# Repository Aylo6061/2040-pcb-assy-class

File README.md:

# 2040pad

An RP2040 macropad, and the board you build in my hands-on PCB soldering class.

## Features

- RP2040 microcontroller with USB-C
- 12 Choc key switches
- 12 SK6812MINI-E RGB LEDs
- PEC11R rotary encoder with push switch
- 128x32 SSD1306 OLED
- QMK firmware

## What's here

| Path | Contents |
|---|---|
| `2040pad/` | KiCad schematic and board, plus `gerbs.zip` |
| `firmware/qmk/2040pad/` | QMK keyboard definition, with build and flashing steps |
| `2040pad_assembly.html`, `2040pad_assembly.pdf` | Soldering and assembly guide |
| `docs/` | [Class web page](https://aylo6061.github.io/2040-pcb-assy-class/) |

The case design is coming soon.

## Status

The first board was built on 2026-11-05, and everything works.

## Credits and license

Based on the [Adafruit MacroPad RP2040](https://github.com/adafruit/Adafruit-MacroPad-RP2040-PCB),
designed by Limor Fried/Ladyada for Adafruit Industries. This is not an Adafruit
product, and Adafruit doesn't support or endorse it.

The hardware is released under Creative Commons Attribution-ShareAlike 3.0.
See [license.txt](license.txt).

The firmware is released under GPL-2.0-or-later. It is based on QMK's
`keyboards/adafruit/macropad` definition, Copyright 2022 Jose Pablo Ramirez.

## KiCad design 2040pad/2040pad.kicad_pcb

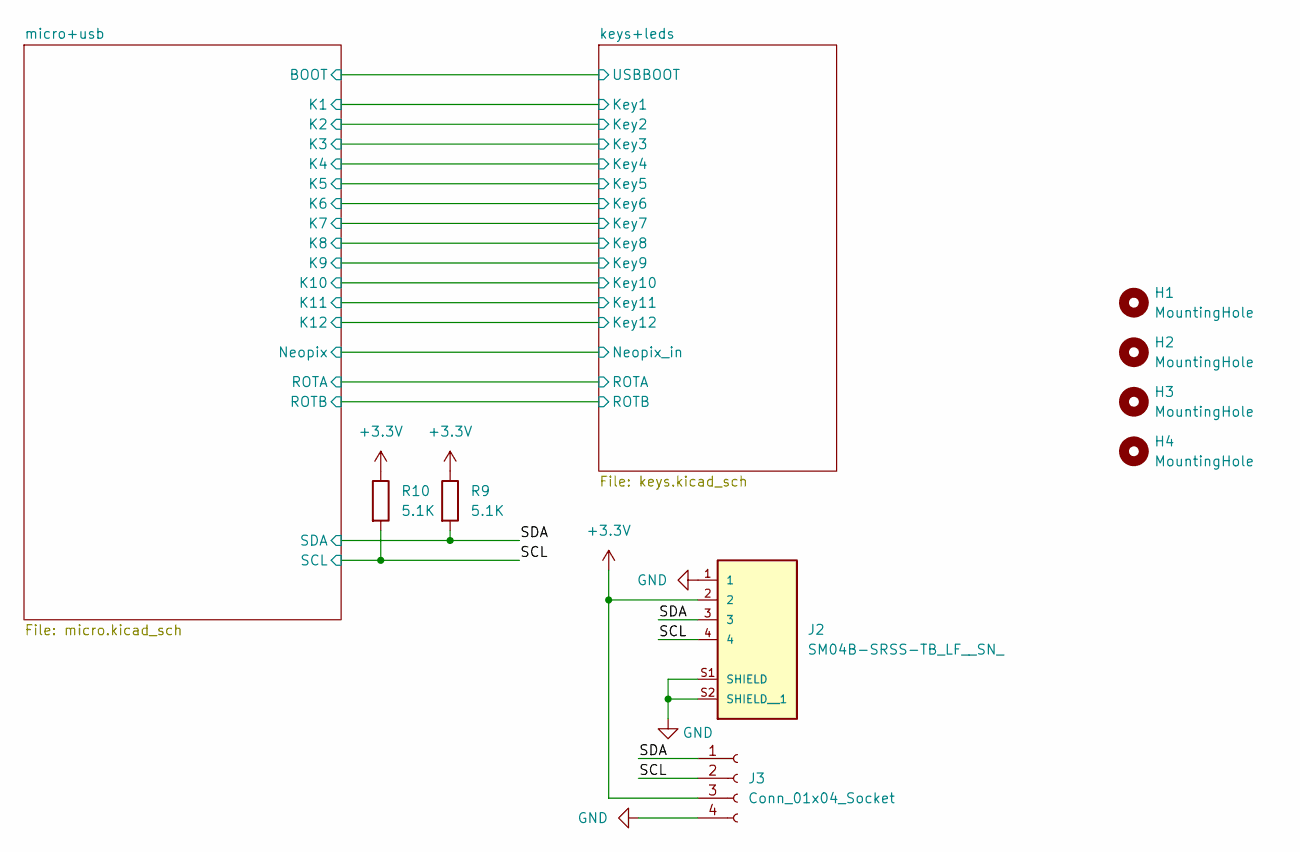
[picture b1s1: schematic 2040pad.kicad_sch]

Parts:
H1, H2, H3, H4: MountingHole; MountingHole_2.2mm_M2
J2: SM04B-SRSS-TB_LF__SN_; JST_SM04B-SRSS-TB_LF__SN_; MPN SM04B-SRSS-TB
J3: Conn_01x04_Socket; Waveshare .91 oled
R9, R10: 5.1K; R_0603_1608Metric; MPN RMCF0603JT5K10

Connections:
+3.3V: J2.2, J3.3, R9.1, R10.1; also elsewhere on the board
/SCL: J2.4, J3.2, R10.2; also elsewhere on the board
/SDA: J2.3, J3.1, R9.2; also elsewhere on the board
GND: J2.1, J2.S1 (SHIELD), J2.S2 (SHIELD__1), J3.4; also elsewhere on the board

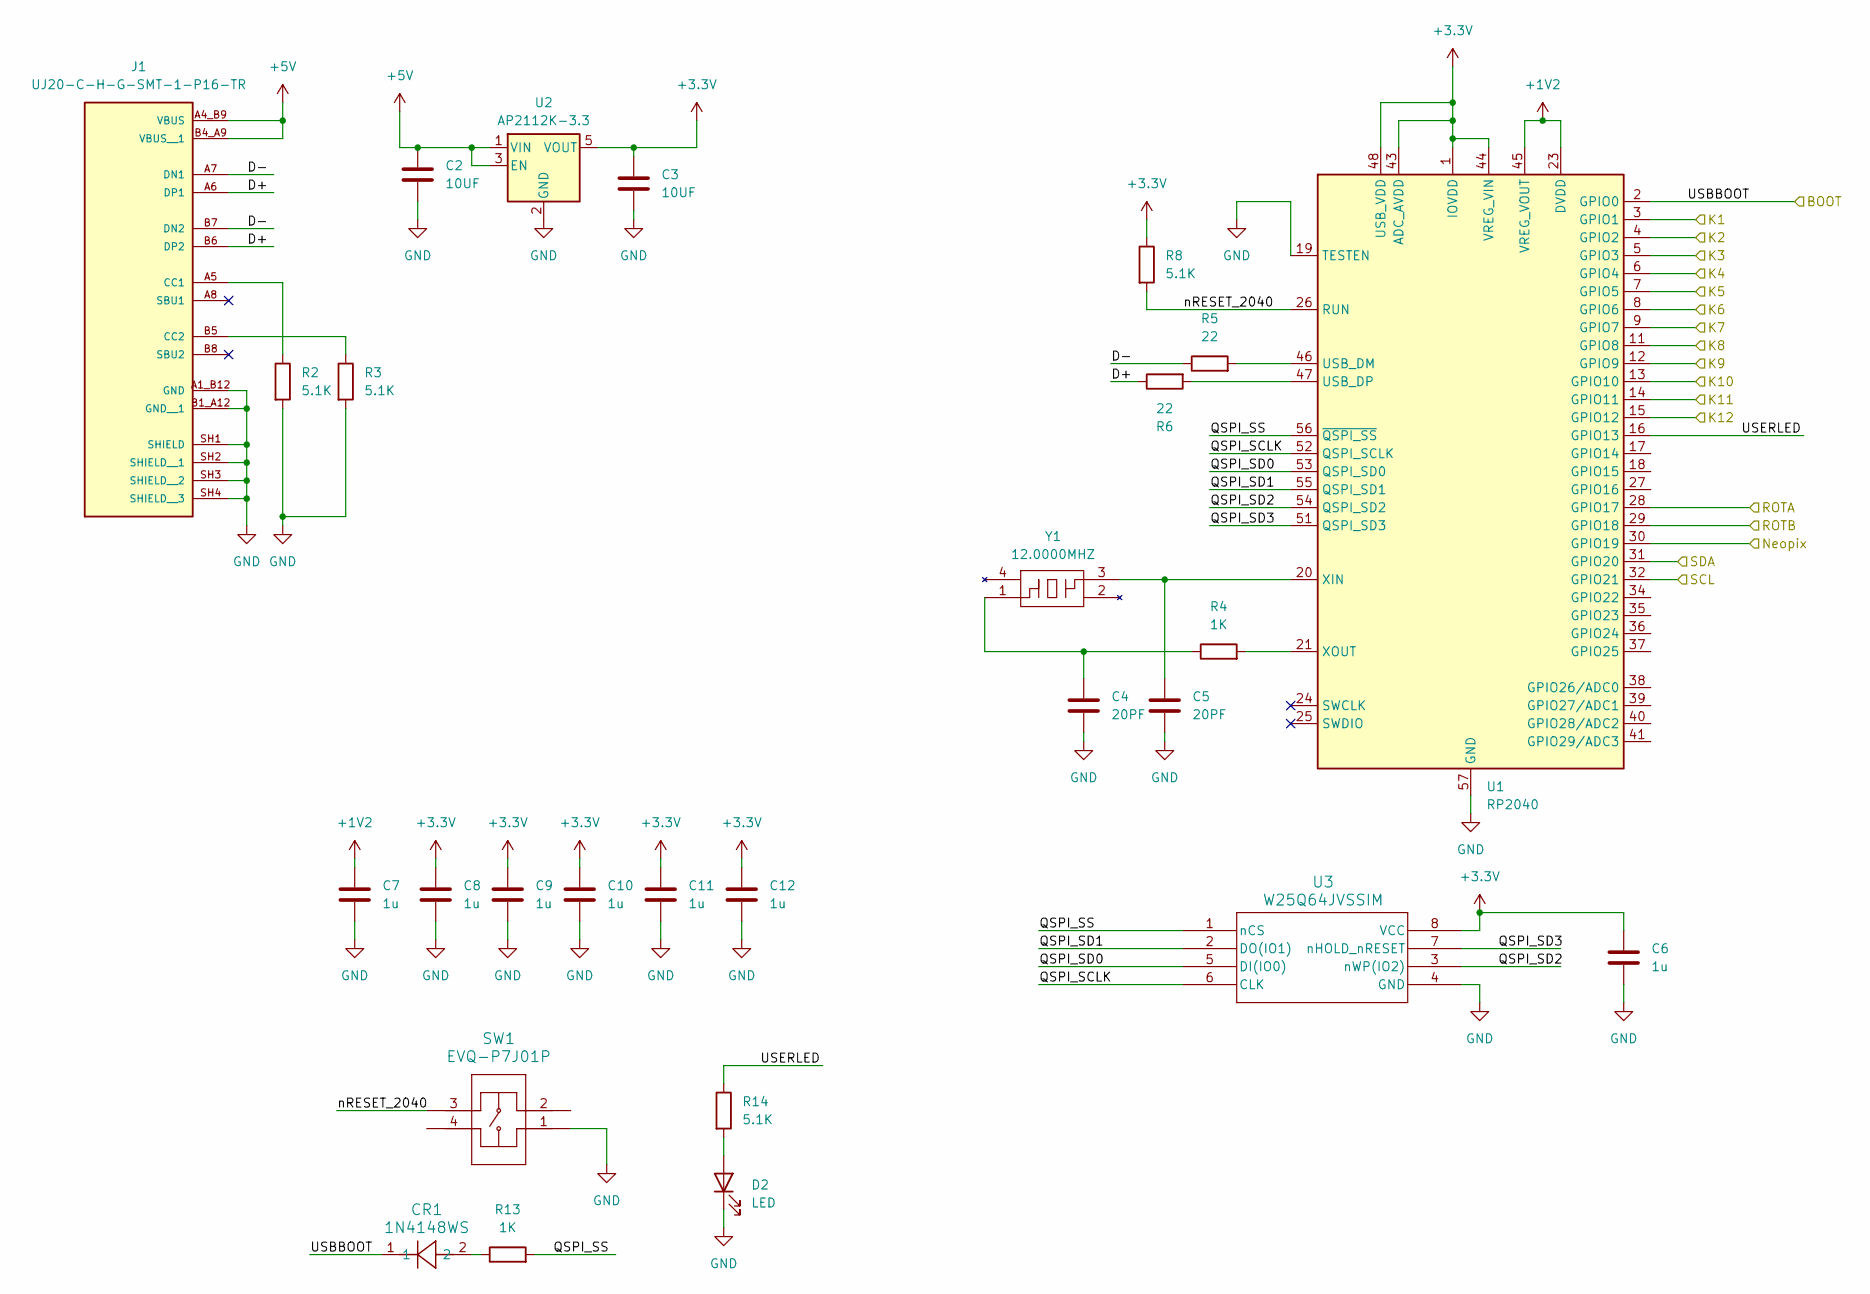
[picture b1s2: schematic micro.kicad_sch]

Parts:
C2, C3: 10UF; C_0805_2012Metric; MPN GRM21BR71A106KA73K
C4, C5: 20PF; R_0603_1608Metric; MPN CL10C200JB8NNNC
C6, C7, C8, C9, C10, C11, C12: 1u; C_0805_2012Metric; MPN CL21B105KAFNNNE
CR1: 1N4148WS; SOD-323FL_ONS; MPN 1N4148WS
D2: LED; LED_0603_1608Metric
J1: UJ20-C-H-G-SMT-1-P16-TR; SAMESKY_UJ20-C-H-G-SMT-1-P16-TR; PARTREV 1.0
R2, R3, R8, R14: 5.1K; R_0603_1608Metric; MPN RMCF0603JT5K10
R4, R13: 1K; R_0603_1608Metric; MPN RMCF0603FG1K00
R5, R6: 22; R_0603_1608Metric; MPN WR06X220 JTL
SW1: EVQ-P7J01P; SMD4_SW_EVQP7J_PAN; MPN EVQ-P7J01P
U1: RP2040; QFN-56-1EP_7x7mm_P0.4mm_EP3.2x3.2mm; MPN SC0914(13)
U2: AP2112K-3.3; SOT-23-5; MPN AP2112K-3.3TRG1
U3: W25Q64JVSSIM; SOIC_208MIL_WIN; MPN W25Q64JVSSIM TR
Y1: 12.0000MHZ; CX3225GB; Mouser Part Number 581-CX3225GB12HKPSC1

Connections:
+1V2: C7.1, U1.23 (DVDD), U1.45 (VREG_VOUT), U1.50 (DVDD)
+3.3V: C3.1, C6.1, C8.1, C9.1, C10.1, C11.1, C12.1, R8.1, U1.1 (IOVDD), U1.10 (IOVDD), U1.22 (IOVDD), U1.33 (IOVDD), U1.42 (IOVDD), U1.43 (ADC_AVDD), U1.44 (VREG_VIN), U1.48 (USB_VDD), U1.49 (IOVDD), U2.5 (VOUT), U3.8 (VCC); also elsewhere on the board
+5V: C2.1, J1.A4_B9 (VBUS), J1.B4_A9 (VBUS__1), U2.1 (VIN), U2.3 (EN); also elsewhere on the board
/SCL: U1.32 (GPIO21); also elsewhere on the board
/SDA: U1.31 (GPIO20); also elsewhere on the board
/keys+leds/Key1: U1.3 (GPIO1); also elsewhere on the board
/keys+leds/Key2: U1.4 (GPIO2); also elsewhere on the board
/keys+leds/Key3: U1.5 (GPIO3); also elsewhere on the board
/keys+leds/Key4: U1.6 (GPIO4); also elsewhere on the board
/keys+leds/Key5: U1.7 (GPIO5); also elsewhere on the board
/keys+leds/Key6: U1.8 (GPIO6); also elsewhere on the board
/keys+leds/Key7: U1.9 (GPIO7); also elsewhere on the board
/keys+leds/Key8: U1.11 (GPIO8); also elsewhere on the board
/keys+leds/Key9: U1.12 (GPIO9); also elsewhere on the board
/keys+leds/Key10: U1.13 (GPIO10); also elsewhere on the board
/keys+leds/Key11: U1.14 (GPIO11); also elsewhere on the board
/keys+leds/Key12: U1.15 (GPIO12); also elsewhere on the board
/keys+leds/Neopix_in: U1.30 (GPIO19); also elsewhere on the board
/keys+leds/ROTA: U1.28 (GPIO17); also elsewhere on the board
/keys+leds/ROTB: U1.29 (GPIO18); also elsewhere on the board
/micro+usb/D+: J1.A6 (DP1), J1.B6 (DP2), R6.1
/micro+usb/D-: J1.A7 (DN1), J1.B7 (DN2), R5.1
/micro+usb/QSPI_SCLK: U1.52 (QSPI_SCLK), U3.6 (CLK)
/micro+usb/QSPI_SD0: U1.53 (QSPI_SD0), U3.5 (DI(IO0))
/micro+usb/QSPI_SD1: U1.55 (QSPI_SD1), U3.2 (DO(IO1))
/micro+usb/QSPI_SD2: U1.54 (QSPI_SD2), U3.3 (nWP(IO2))
/micro+usb/QSPI_SD3: U1.51 (QSPI_SD3), U3.7 (nHOLD_nRESET)
/micro+usb/QSPI_SS: R13.2, U1.56 (~QSPI_SS), U3.1 (nCS)
/micro+usb/USBBOOT: CR1.1, U1.2 (GPIO0); also elsewhere on the board
/micro+usb/USERLED: R14.1, U1.16 (GPIO13)
/micro+usb/nRESET_2040: R8.2, SW1.3, U1.26 (RUN)
GND: C2.2, C3.2, C4.2, C5.2, C6.2, C7.2, C8.2, C9.2, C10.2, C11.2, C12.2, D2.1 (K), J1.A1_B12 (GND), J1.B1_A12 (GND__1), J1.SH1 (SHIELD), J1.SH2 (SHIELD__1), J1.SH3 (SHIELD__2), J1.SH4 (SHIELD__3), R2.2, R3.2, SW1.1, U1.19 (TESTEN), U1.57 (GND), U2.2 (GND), U3.4 (GND); also elsewhere on the board
unnamed: C4.1, R4.1, Y1.1
unnamed: CR1.2, R13.1
unnamed: D2.2 (A), R14.2
unnamed: J1.A5 (CC1), R2.1
unnamed: J1.B5 (CC2), R3.1
unnamed: R5.2, U1.46 (USB_DM)
unnamed: R6.2, U1.47 (USB_DP)
unnamed: C5.1, U1.20 (XIN), Y1.3
unnamed: R4.2, U1.21 (XOUT)

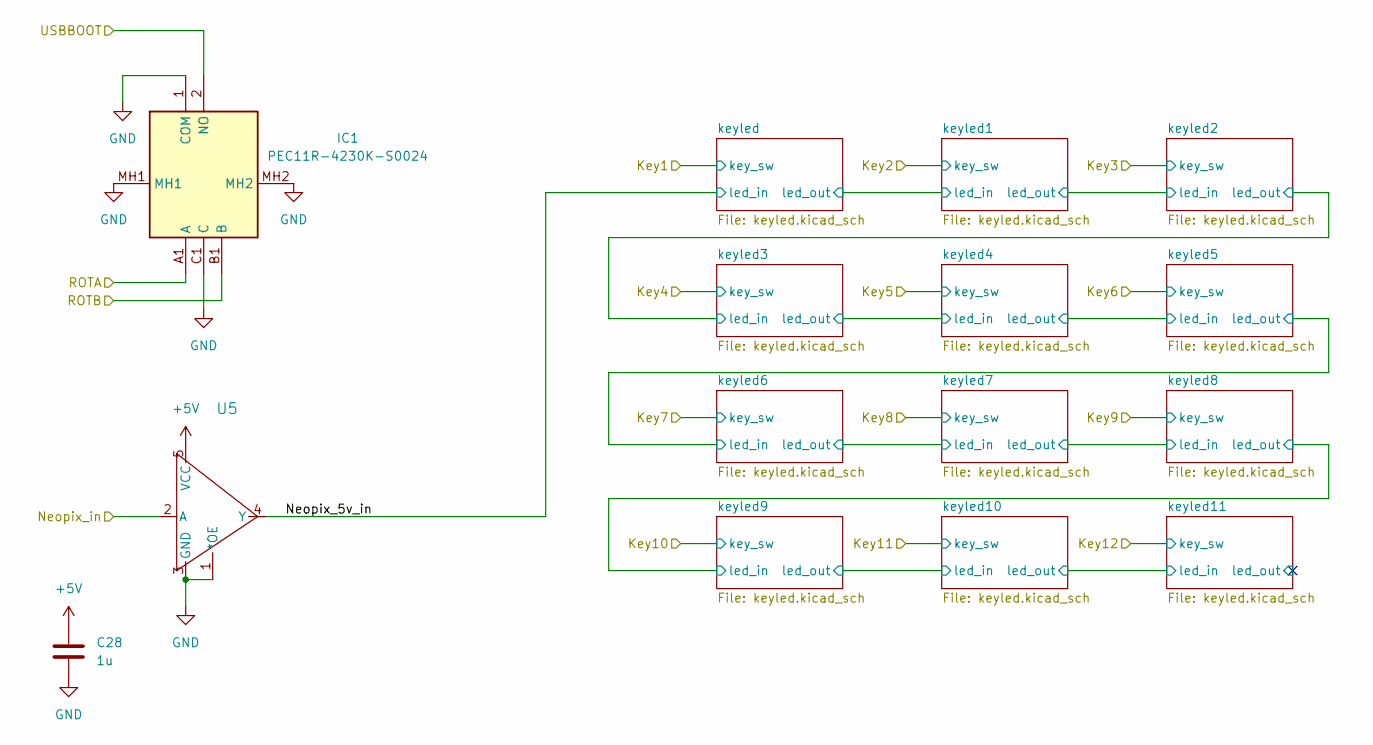
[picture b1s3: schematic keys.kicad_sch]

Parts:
C28: 1u; C_0805_2012Metric; MPN CL21B105KAFNNNE
IC1: PEC11R-4230K-S0024; PEC11R4230KS0024; Mouser Part Number 652-PEC11R4230KS0024
U5: SN74AHCT1G125DBVR; DBV5; MPN SN74AHCT1G125DBVR

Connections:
+5V: C28.1, U5.5 (VCC); also elsewhere on the board
/keys+leds/Neopix_5v_in: U5.4 (Y); also elsewhere on the board
/keys+leds/Neopix_in: U5.2 (A); also elsewhere on the board
/keys+leds/ROTA: IC1.A1 (A); also elsewhere on the board
/keys+leds/ROTB: IC1.B1 (B); also elsewhere on the board
/micro+usb/USBBOOT: IC1.2 (NO); also elsewhere on the board
GND: C28.2, IC1.1 (COM), IC1.C1 (C), IC1.MH1, IC1.MH2, U5.1 (*OE), U5.3 (GND); also elsewhere on the board

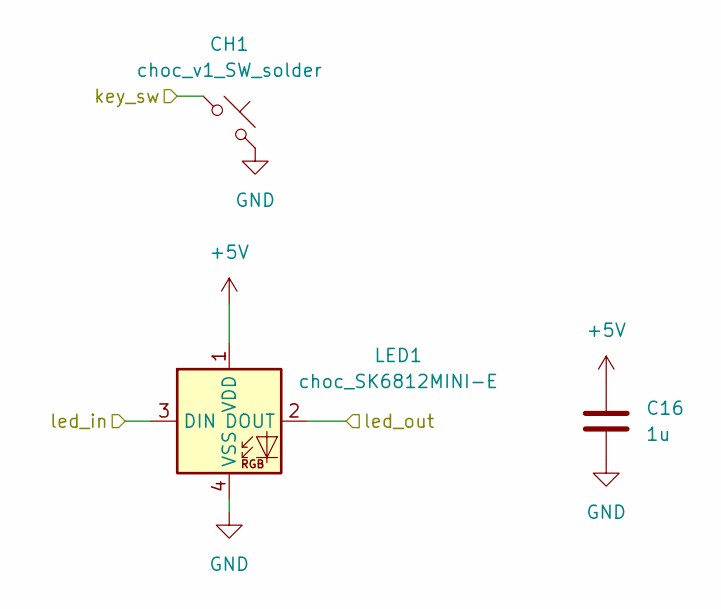
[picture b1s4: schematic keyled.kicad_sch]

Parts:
C16: 1u; C_0805_2012Metric
CH1: choc_v1_SW_solder; SW_choc_v1_1u
LED1: choc_SK6812MINI-E; LED_choc_6028R

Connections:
+5V: C16.1, LED1.1 (VDD); also elsewhere on the board
/keys+leds/Key1: CH1.1; also elsewhere on the board
/keys+leds/Neopix_5v_in: LED1.3 (DIN); also elsewhere on the board
/keys+leds/keyled/led_out: LED1.2 (DOUT); also elsewhere on the board
GND: C16.2, CH1.2, LED1.4 (VSS); also elsewhere on the board

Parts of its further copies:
C17, C18, C19, C20, C21, C22, C23, C24, C25, C26, C27: 1u; C_0805_2012Metric
CH2, CH3, CH4, CH5, CH6, CH7, CH8, CH9, CH10, CH11, CH12: choc_v1_SW_solder; SW_choc_v1_1u
LED2, LED3, LED4, LED5, LED6, LED7, LED8, LED9, LED10, LED11, LED12: choc_SK6812MINI-E; LED_choc_6028R

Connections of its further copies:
+5V: C17.1, C18.1, C19.1, C20.1, C21.1, C22.1, C23.1, C24.1, C25.1, C26.1, C27.1, LED2.1 (VDD), LED3.1 (VDD), LED4.1 (VDD), LED5.1 (VDD), LED6.1 (VDD), LED7.1 (VDD), LED8.1 (VDD), LED9.1 (VDD), LED10.1 (VDD), LED11.1 (VDD), LED12.1 (VDD); also elsewhere on the board
/keys+leds/Key2: CH2.1; also elsewhere on the board
/keys+leds/Key3: CH3.1; also elsewhere on the board
/keys+leds/Key4: CH4.1; also elsewhere on the board
/keys+leds/Key5: CH5.1; also elsewhere on the board
/keys+leds/Key6: CH6.1; also elsewhere on the board
/keys+leds/Key7: CH7.1; also elsewhere on the board
/keys+leds/Key8: CH8.1; also elsewhere on the board
/keys+leds/Key9: CH9.1; also elsewhere on the board
/keys+leds/Key10: CH10.1; also elsewhere on the board
/keys+leds/Key11: CH11.1; also elsewhere on the board
/keys+leds/Key12: CH12.1; also elsewhere on the board
/keys+leds/keyled1/led_out: LED2.2 (DOUT), LED3.3 (DIN)
/keys+leds/keyled2/led_out: LED3.2 (DOUT), LED4.3 (DIN)
/keys+leds/keyled3/led_out: LED4.2 (DOUT), LED5.3 (DIN)
/keys+leds/keyled4/led_out: LED5.2 (DOUT), LED6.3 (DIN)
/keys+leds/keyled5/led_out: LED6.2 (DOUT), LED7.3 (DIN)
/keys+leds/keyled6/led_out: LED7.2 (DOUT), LED8.3 (DIN)
/keys+leds/keyled7/led_out: LED8.2 (DOUT), LED9.3 (DIN)
/keys+leds/keyled8/led_out: LED9.2 (DOUT), LED10.3 (DIN)
/keys+leds/keyled10/led_in: LED10.2 (DOUT), LED11.3 (DIN)
/keys+leds/keyled10/led_out: LED11.2 (DOUT), LED12.3 (DIN)
/keys+leds/keyled11/led_out: LED12.2 (DOUT)
/keys+leds/keyled/led_out: LED2.3 (DIN); also elsewhere on the board
GND: C17.2, C18.2, C19.2, C20.2, C21.2, C22.2, C23.2, C24.2, C25.2, C26.2, C27.2, CH2.2, CH3.2, CH4.2, CH5.2, CH6.2, CH7.2, CH8.2, CH9.2, CH10.2, CH11.2, CH12.2, LED2.4 (VSS), LED3.4 (VSS), LED4.4 (VSS), LED5.4 (VSS), LED6.4 (VSS), LED7.4 (VSS), LED8.4 (VSS), LED9.4 (VSS), LED10.4 (VSS), LED11.4 (VSS), LED12.4 (VSS); also elsewhere on the board

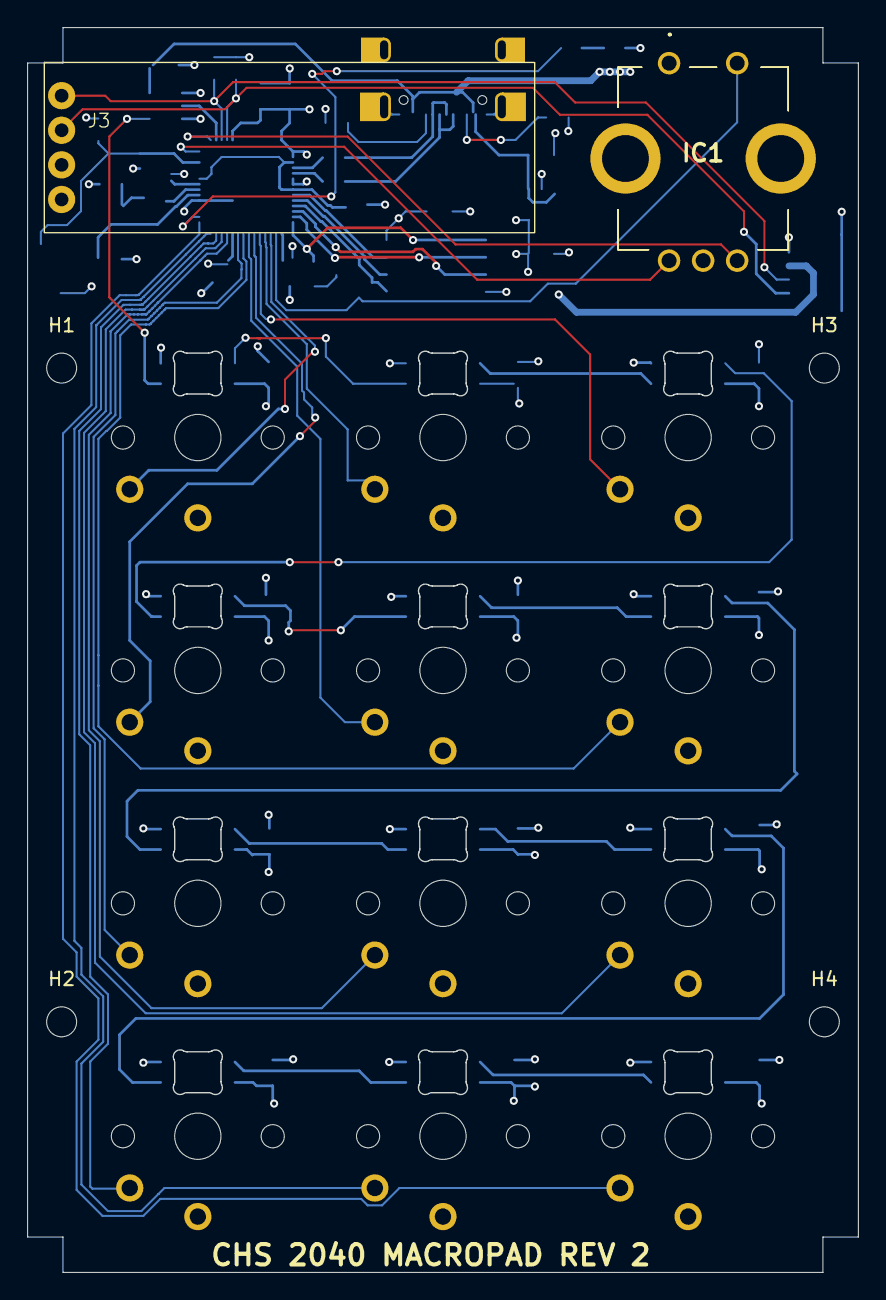
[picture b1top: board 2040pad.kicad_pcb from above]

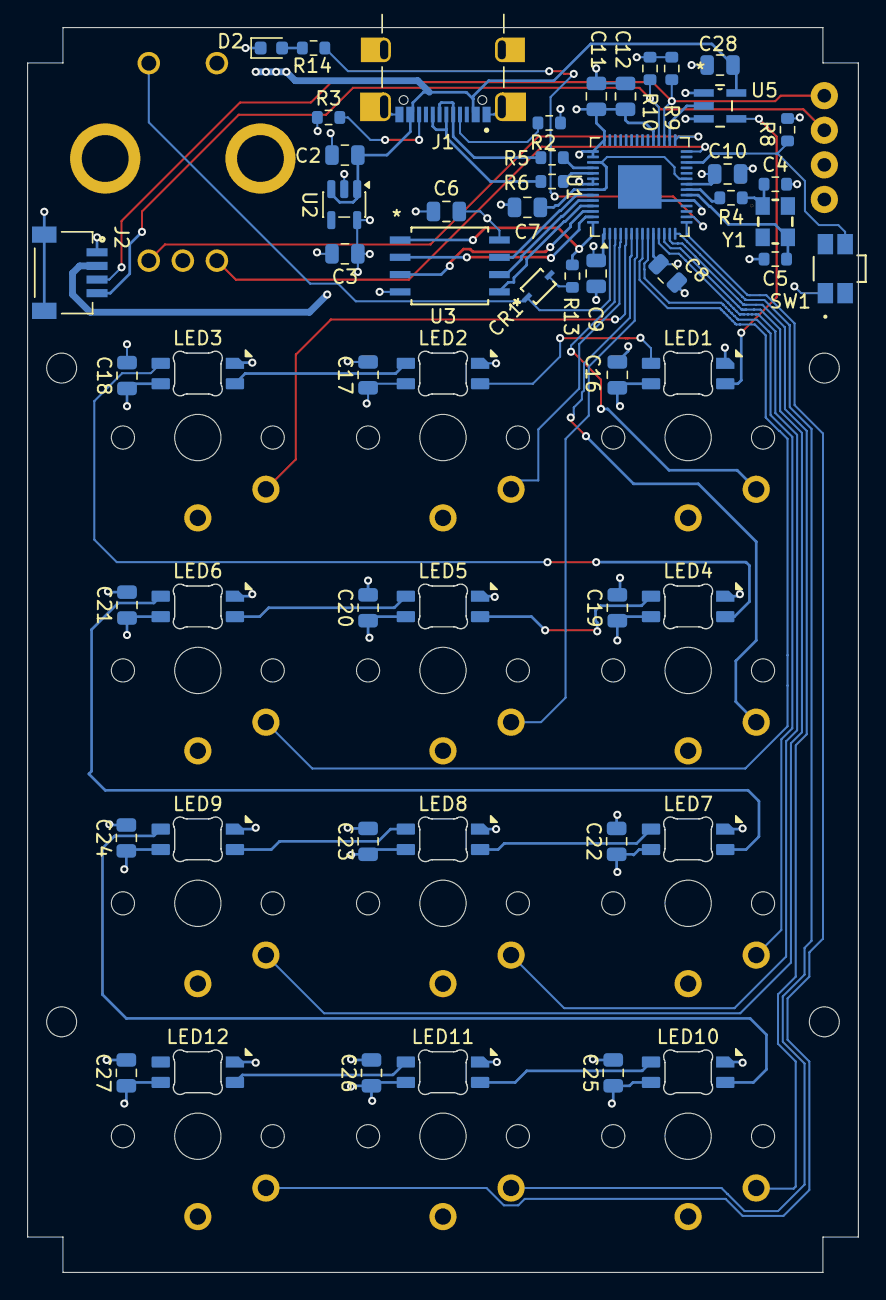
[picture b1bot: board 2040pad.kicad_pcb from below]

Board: 4 copper layers, 61.0 x 91.4 mm, 74 parts (56 on the bottom side), 53 nets.
